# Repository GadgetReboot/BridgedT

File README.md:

# BridgedT
Bridged T Oscillator

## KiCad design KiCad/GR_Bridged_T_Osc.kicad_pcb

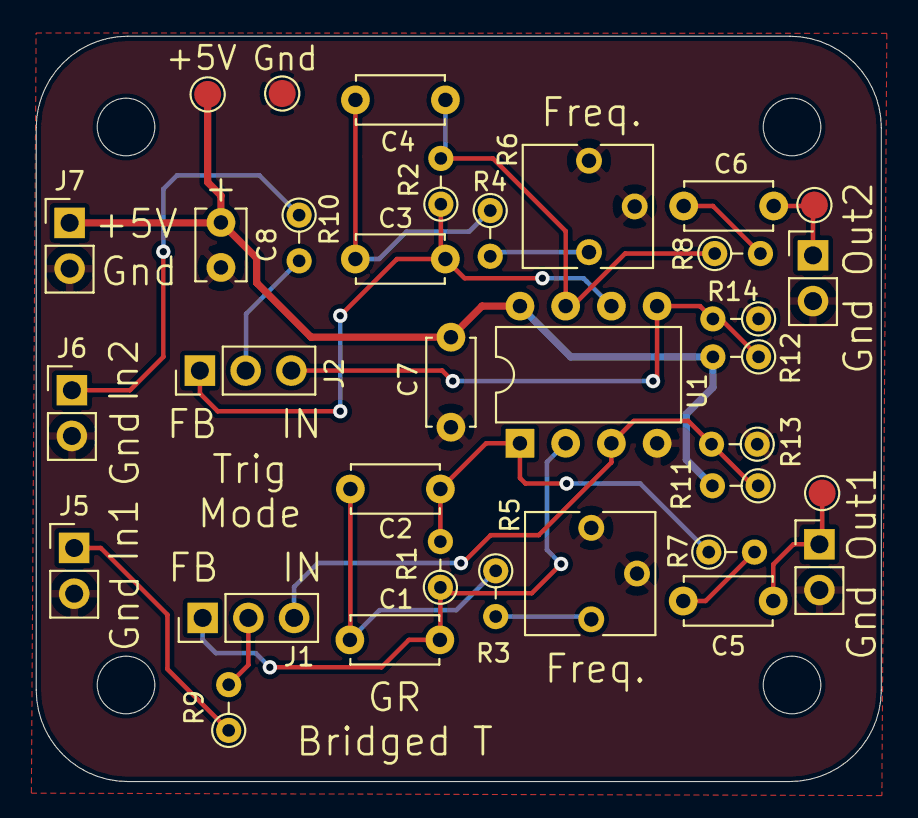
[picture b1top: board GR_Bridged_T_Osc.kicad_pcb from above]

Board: 2 copper layers, 46.9 x 41.4 mm, 38 parts (0 on the bottom side), 20 nets.

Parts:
C1, C2, C3, C4: 33n; C_Disc_D4.7mm_W2.5mm_P5.00mm
C5, C6: 680nF; C_Disc_D4.7mm_W2.5mm_P5.00mm
C7: 100nF; C_Disc_D4.7mm_W2.5mm_P5.00mm
C8: 4.7uF; C_Disc_D3.8mm_W2.6mm_P2.50mm
J1, J2: Conn_01x03; PinHeader_1x03_P2.54mm_Vertical
J3, J4, J5, J6, J7: Conn_01x02; PinHeader_1x02_P2.54mm_Vertical
MH1, MH2, MH3, MH4: MountingHole; MountingHole_3.2mm_M3
R1, R2: 4M; R_Axial_DIN0204_L3.6mm_D1.6mm_P2.54mm_Vertical
R3, R4: 100; R_Axial_DIN0204_L3.6mm_D1.6mm_P2.54mm_Vertical
R5, R6: 10K; Potentiometer_Vishay_T73YP_Vertical
R7, R8: 100r; R_Axial_DIN0204_L3.6mm_D1.6mm_P2.54mm_Vertical
R9, R10, R11, R12: 10K; R_Axial_DIN0204_L3.6mm_D1.6mm_P2.54mm_Vertical
R13, R14: 4K3; R_Axial_DIN0204_L3.6mm_D1.6mm_P2.54mm_Vertical
TP1, TP2, TP3, TP4: TestPoint; TestPoint_Pad_D1.5mm
U1: LM358; DIP-8_W7.62mm

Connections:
+5V: C7.1, C8.1, J7.1, R11.2, R12.2, TP1.1, U1.8
/In1: J5.1, R9.1
/In2: J6.1, R10.1
/Out1: C5.1, J3.1, TP2.1
/Out2: C6.1, J4.1, TP3.1
GNDREF: C7.2, C8.2, J3.2, J4.2, J5.2, J6.2, J7.2, R5.2, R5.3, R6.2, R6.3, R13.1, R14.1, TP4.1, U1.4
unnamed: C1.1, C2.2, R3.1
unnamed: C1.2, J1.1, R1.1, U1.2
unnamed: C2.1, R1.2, R7.1, U1.1
unnamed: C3.1, C4.2, R4.1
unnamed: C3.2, J2.1, R2.1, U1.6
unnamed: C4.1, R2.2, R8.1, U1.7
unnamed: C5.2, R7.2
unnamed: C6.2, R8.2
unnamed: J1.2, R9.2
unnamed: J1.3, R11.1, R13.2, U1.3
unnamed: J2.2, R10.2
unnamed: J2.3, R12.1, R14.2, U1.5
unnamed: R3.2, R5.1
unnamed: R4.2, R6.1
